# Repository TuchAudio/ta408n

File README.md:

# ta408n
Compact, simple Volume &amp; Balance control

## Purpose
This is intended to be placed between an _Input Selection board_ like [TuchAudio 509](../../../ta509) and a _power amp_ stage, like a couple of [TuchAudio 209](../../../ta209) boards. This is the recommended configuration as in the [TuchAudio 309](../../../ta309) _Integrated Amplifier_ .

Being a **totally passive** circuit, it might be used with almost any other configuration, like the [501](../../../ta501) board.

### Options and improvements
A possible upgrade would be the [TuchAudio 409n](../../../ta409n) board, which replaces the _balance_ control for a _switchable_ **tone control** (Baxandall-type).

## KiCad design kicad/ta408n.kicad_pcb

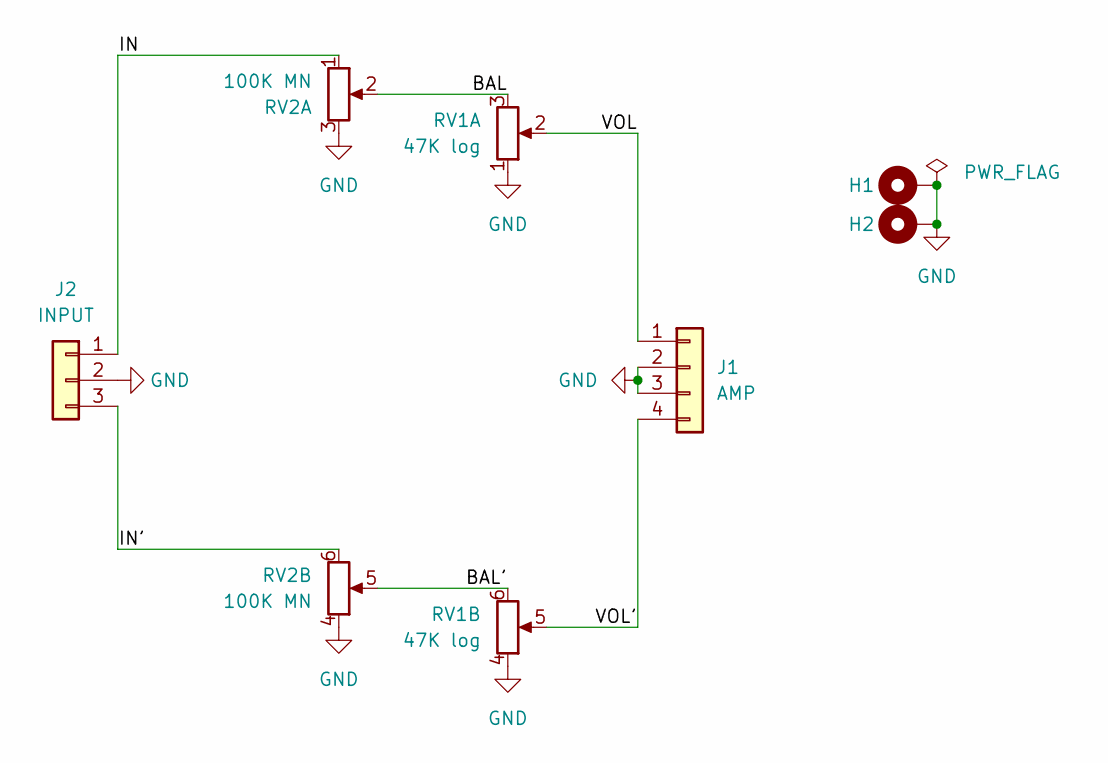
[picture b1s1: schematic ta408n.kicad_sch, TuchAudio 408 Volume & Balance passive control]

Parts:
H1, H2: MountingHole_Pad; MountingHole_3.2mm_M3_DIN965_Pad
J1: AMP; PinHeader_1x04_P2.54mm_Vertical
J2: INPUT; PinHeader_1x03_P2.54mm_Vertical
RV1: 47K log; Potentiometer_Alps_225G_Dual_Horizontal
RV2: 100K MN; Potentiometer_Alps_225G_Dual_Horizontal

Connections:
/BAL: RV1.3, RV2.2
/BAL': RV1.6, RV2.5
/IN: J2.1, RV2.1
/IN': J2.3, RV2.6
/VOL: J1.1, RV1.2
/VOL': J1.4, RV1.5
GND: H1.1, H2.1, J1.2, J1.3, J2.2, RV1.1, RV1.4, RV2.3, RV2.4

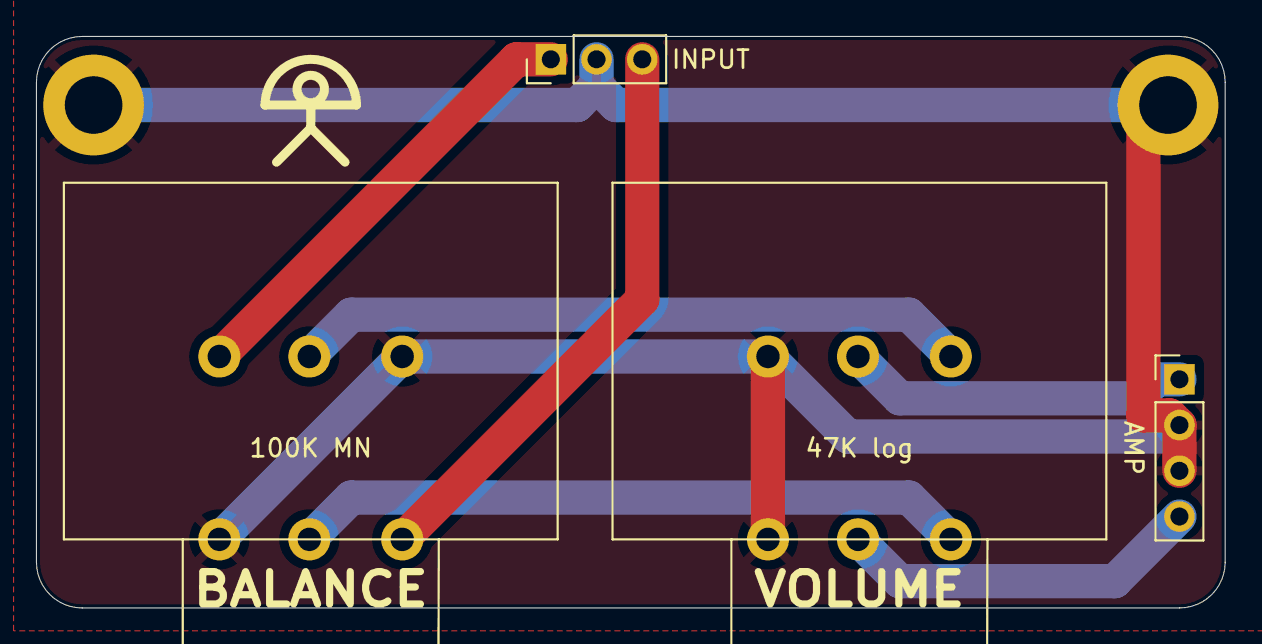
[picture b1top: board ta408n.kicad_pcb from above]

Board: 2 copper layers, 66.0 x 31.8 mm, 6 parts (0 on the bottom side), 7 nets.

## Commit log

2025-11-08 add KiCAD files
2025-11-12 purpose and options
2025-11-24 add links
